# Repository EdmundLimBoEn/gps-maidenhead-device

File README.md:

# Maidenhead Pocket Locator

Open hardware and software for a compact GNSS-powered six-character Maidenhead
locator. The product requirements and validation gates live in [PLAN.md](PLAN.md).

## Current status

The development source tree covers RP2040 firmware and host tests, a
Tk/serial configurator with profiles and UF2 recovery, KiCad engineering sources
and manufacturing workflow, a parametric enclosure with printable exports, and
assembly/validation documentation.

This is **not yet a physically validated product release**. Ordering and public
distribution remain gated on the frozen BOM/quote, reviewed manufacturing exports,
prototype bring-up, and measured acceptance evidence listed in
[the release checklist](docs/manufacturing/RELEASE_CHECKLIST.md) and
[evidence index](docs/testing/TEST_EVIDENCE.md). No claim is made here that the
weather, battery, GNSS, off-current, thermal, or cost gates have passed.

## Development

```sh
cmake -S firmware -B .build/firmware
cmake --build .build/firmware
ctest --test-dir .build/firmware --output-on-failure

python -m venv .venv
. .venv/bin/activate
python -m pip install -e './configurator[dev]'
pytest configurator/tests
python -m ruff check configurator tools
python -m ruff format --check configurator tools
python -m maidenhead_configurator

bash firmware/tests/pico_stub_compile.sh
python3 hardware/manufacturing/preflight.py
python3 tools/export_enclosure.py
python3 tools/validate_enclosure.py --require-openscad
python3 tools/check_docs.py
python3 tools/release_preflight.py
```

To build an RP2040 UF2, install the Pico SDK and set its location:

```sh
PICO_SDK_PATH=/path/to/pico-sdk \
  cmake -S firmware -B .build/firmware-pico -DPOCKET_LOCATOR_BUILD_RP2040=ON
cmake --build .build/firmware-pico
```

The GUI starts against a simulator by default. A physical device uses
newline-delimited JSON over USB CDC; each configuration write includes a fresh
15-year named-zone transition table. Profiles remain location-free and portable.

## Manufacturing and safety

Do not order or distribute from an arbitrary working tree. Generate artifacts from
a tagged revision, complete [the five-unit order package](docs/manufacturing/ORDER_PACKAGE.md),
and follow the [assembly](docs/assembly/ASSEMBLY.md) and
[test procedures](docs/testing/TEST_PROCEDURES.md).

The [mechanical interface contract](enclosure/INTERFACES.md) and
[cost research snapshot](docs/manufacturing/COST_RESEARCH.md) make the remaining
fit and landed-cost unknowns explicit. Neither is a manufacturing sign-off.

Use only the released protected LiPo and charger configuration. The device is not
an emergency locator, navigation instrument, tracker, or immersion-rated product.
Do not charge it while wet or leave it charging in a hot vehicle.

## Licensing

Firmware and configurator code are GPL-3.0-or-later. Hardware and mechanical
sources are CERN-OHL-S-2.0. Documentation is CC-BY-SA-4.0. See [LICENSES](LICENSES/README.md).

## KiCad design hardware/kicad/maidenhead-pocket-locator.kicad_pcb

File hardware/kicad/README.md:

# Hardware design source

SPDX-License-Identifier: CERN-OHL-S-2.0

This directory contains the revision-A *engineering* KiCad source for the
Maidenhead Pocket Locator.  It is deliberately a source-controlled design,
not by itself a claim that an assembled product has been validated: the selected
LCD, patch antenna, cell and enclosure still require physical fit checks. No RF,
power, charger or thermal measurement has been performed on assembled hardware.

`design.yaml` is a review summary of the electrical architecture and constraints;
the component/pin contract is embedded in `generate_kicad.py`. The generator
writes the legacy schematic and cache while preserving the authoritative routed
PCB. Passing `--force-placement` explicitly replaces the PCB with its
deterministic unrouted placement. The source set contains:

* `maidenhead-pocket-locator.sch` — deterministic legacy Eeschema source;
* `maidenhead-pocket-locator.kicad_sch` — the committed modern KiCad source,
  synchronized from the legacy source with KiCad and used for PDF/netlist exports;
* `maidenhead-pocket-locator.kicad_pcb` — the authoritative routed 4-layer,
  81 x 37 mm board with edge connectors, test points and controlled RF/USB
  net classes. The default manufacturing preflight requires zero DRC errors,
  zero unconnected items, filled inner planes, no signal tracks on In1, and
  only the length-bounded `LCD_RS_3V3`, `LOCATE_N`, `QSPI_SCLK`, and
  `QSPI_SD2` crossovers on In2.

The generated board is useful for electrical/mechanical review and routing
iteration. It must not be sent to a fabricator until the
release checklist passes.  `../manufacturing/export.sh` runs the KiCad CLI
exports and DRC when KiCad is installed.

## Regenerate and inspect

```sh
python3 hardware/kicad/generate_kicad.py
# After an intentional electrical edit, open the legacy .sch in the pinned KiCad
# version, save the converted modern .kicad_sch, and run preflight to compare them.
# Only when intentionally restarting layout:
python3 hardware/kicad/generate_kicad.py --force-placement
python3 hardware/manufacturing/preflight.py --source-only
python3 hardware/manufacturing/preflight.py
kicad hardware/kicad/maidenhead-pocket-locator.kicad_pro
```

The source-only command is a diagnostic aid. CI and manufacturing exports use
the strict default command; it must pass before manufacturing exports are
accepted.

The board datum is the lower-left outside corner.  LCD/window centre is
`(40.5, 18.5)`.  The antenna is an enclosure-mounted patch, not a PCB
component; its 50-ohm route ends at J4.  Keep the top-wall patch projection
clear of copper and parts as documented in `../RF_AND_LAYOUT.md`.

The controlled stack is F.Cu signal/power, In1 uninterrupted GND reference,
In2 predominantly 3V3 power distribution, and B.Cu signal/GND. In2 carries only
the under-7 mm LCD RS, under-4 mm LOCATE, and under-6 mm QSPI SCLK/SD2
crossovers allowlisted by preflight. USB and GNSS RF stay on outer copper over
In1; the short QSPI inner runs also reference the uninterrupted In1 plane. Obtain
the fabricator's impedance calculation before release; nominal
trace widths in the source are starting values, not a substitute for a coupon.
Ordinary logic uses 0.15 mm traces and 0.50/0.20 mm through-vias. Dense QSPI
fanout uses 0.10 mm traces and local 0.46/0.20 mm standard through-vias; confirm
the 0.13 mm annular ring with the selected fabricator. The edge rule
is 0.20 mm for the unavoidable short escapes at J1, SW1 and SW2; confirm both
capabilities in the selected board quote.

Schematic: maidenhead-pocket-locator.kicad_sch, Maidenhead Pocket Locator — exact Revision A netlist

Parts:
C1, C2, C3, C4, C5, C6, C7, C8, C9: 100nF; C_0402_1005Metric
CADC1: 1uF; C_0603_1608Metric
CBAT1: 4.7uF; C_0603_1608Metric
CBATADC1: 100nF; C_0402_1005Metric
CBBIN1: 10uF; C_0805_2012Metric
CBBOUT1: 22uF; C_0805_2012Metric
CDV1, CDV2: 100nF; C_0402_1005Metric
CFLASH1: 100nF; C_0402_1005Metric
CGIN1: 1uF; C_0402_1005Metric
CGNSS1: 100nF; C_0402_1005Metric
CGNSS2: 820pF; C_0402_1005Metric
CGNSS3: 10uF; C_0805_2012Metric
CGOUT1: 4.7uF; C_0603_1608Metric
CIN1: 1uF; C_0603_1608Metric
CLCDIN1: 10uF; C_0805_2012Metric
CLCDO1, CLCDO2: 10uF; C_0805_2012Metric
COUT1: 4.7uF; C_0603_1608Metric
CRESET1: 100nF; C_0402_1005Metric
CULD1: 100nF; C_0402_1005Metric
CULS1: 100nF; C_0402_1005Metric
CVREG1: 1uF; C_0603_1608Metric
CX1, CX2: 15pF; C_0402_1005Metric
D1: TPD2EUSB30DRTR; Texas_DRT0003A
D2, D4: BAT54H; D_SOD-323
D3, D5: 1N4148WS; D_SOD-323
F1: MF-MSMF050-2; Fuse_1812_4532Metric
J1: USB4105-GF-A
J2: B3B-PH-K-S(LF)(SN); JST_PH_B3B-PH-K_1x03_P2.00mm_Vertical
J3: 61301611121; PinHeader_1x16_P2.54mm_Vertical
J4: Hirose 20449-001E; U.FL_Hirose_U.FL-R-SMT-1_Vertical
LBB1: XFL4020-471MEC; L_Coilcraft_XxL4020
LED1: KP-2012EC; LED_0805_2012Metric
LLCD1: LQH2MCN1R0M02L; L_0805_2012Metric
Q1, Q4: DMP3098L-7; SOT-23
Q2, Q3, Q5: DMN2050L-7; SOT-23
RBAT1, RBAT2: 100k; R_0402_1005Metric
RBATG1: 100k; R_0402_1005Metric
RBB1: 511k; R_0402_1005Metric
RBB2: 91k; R_0402_1005Metric
RBL1: 68R; R_0603_1608Metric
RBOOT1: 1k; R_0402_1005Metric
RCC1, RCC2: 5.1k; R_0402_1005Metric
RCHG1: 1k; R_0402_1005Metric
RCHGPU1: 100k; R_0402_1005Metric
REN1: 1M; R_0402_1005Metric
RGNSSEN1: 100k; R_0402_1005Metric
RGNSSRX1: 33R; R_0402_1005Metric
RGNSSTX1: 33R; R_0402_1005Metric
RHOLD1: 100k; R_0402_1005Metric
RILIM1: 2.00k; R_0402_1005Metric
RISET1: 2.20k; R_0402_1005Metric
RITERM1: 3.30k; R_0402_1005Metric
RLCD1: 909k; R_0402_1005Metric
RLCD2: 100k; R_0402_1005Metric
RLCDEN1: 100k; R_0402_1005Metric
RLOC1: 100k; R_0402_1005Metric
ROFF1: 100k; R_0402_1005Metric
RRESET1: 100k; R_0402_1005Metric
RSENSEEN1: 100k; R_0402_1005Metric
RSTART1: 100k; R_0402_1005Metric
RTMR1: 48.7k; R_0402_1005Metric
RUSB1, RUSB2: 27R; R_0402_1005Metric
RVB1: 82k; R_0402_1005Metric
RVB2: 100k; R_0402_1005Metric
RVO1: 4.7k; R_0402_1005Metric
RVO2: 560R; R_0402_1005Metric
RXTAL1: 1k; R_0402_1005Metric
SW1, SW2: TL1014BF160QG; SW_TL1014B
SW3, SW4: EVQ-P7A01P; SW_SPST_EVQP7A
TH1: 10k NTC DNP; R_0603_1608Metric
TP1: VBUS; TestPoint_Pad_D1.5mm
TP2: BAT; TestPoint_Pad_D1.5mm
TP3: SYS_RAW; TestPoint_Pad_D1.5mm
TP4: 3V3; TestPoint_Pad_D1.5mm
TP5: 5V_LCD; TestPoint_Pad_D1.5mm
TP6: GND; TestPoint_Pad_D1.5mm
TP7: POWER_HOLD; TestPoint_Pad_D1.5mm
TP8: GNSS_TX; TestPoint_Pad_D1.5mm
TP9: GNSS_RX; TestPoint_Pad_D1.5mm
TP10: SWDIO; TestPoint_Pad_D1.5mm
TP11: SWCLK; TestPoint_Pad_D1.5mm
TP12: RUN_N; TestPoint_Pad_D1.5mm
TP13: BOOTSEL_N; TestPoint_Pad_D1.5mm
U1: RP2040; QFN-56-1EP_7x7mm_P0.4mm_EP3.2x3.2mm
U2: W25Q16JVUXIQ; Winbond_UX_8
U3: BQ24074RGTR; Texas_RGT0016C
U4: TPS63802DLAR; Texas_DLA0010A
U5: TPS61023DRLR; SOT-563
U6: SN74LVC8T245PWR; TSSOP-24_4.4x7.8mm_P0.65mm
U7: Ai-Thinker GP-02; GP-02
U8: TPS22916BYFPR; Texas_YFP0004
X1: ABM8-272-T3; Crystal_SMD_Abracon_ABM8G-4Pin_3.2x2.5mm

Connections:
1V1: CDV1.1 (1V1), CDV2.1 (1V1), CVREG1.1 (1V1), U1.23 (1V1), U1.45 (1V1), U1.50 (1V1)
3V3: C1.1 (3V3), C2.1 (3V3), C3.1 (3V3), C4.1 (3V3), C5.1 (3V3), C6.1 (3V3), C7.1 (3V3), C8.1 (3V3), C9.1 (3V3), CADC1.1 (3V3), CBBOUT1.1 (3V3), CFLASH1.1 (3V3), CGIN1.1 (3V3), CULS1.1 (3V3), RBB1.1 (3V3), RCHG1.1 (3V3), RCHGPU1.1 (3V3), RLOC1.1 (3V3), ROFF1.1 (3V3), RRESET1.1 (3V3), TP4.1, U1.1 (3V3), U1.10 (3V3), U1.22 (3V3), U1.33 (3V3), U1.42 (3V3), U1.43 (3V3), U1.44 (3V3), U1.48 (3V3), U1.49 (3V3), U2.8 (3V3), U4.6 (3V3), U6.1 (3V3), U6.2 (3V3), U8.A2 (3V3)
3V3_GNSS: CGNSS1.1 (3V3_GNSS), CGNSS2.1 (3V3_GNSS), CGNSS3.1 (3V3_GNSS), CGOUT1.1 (3V3_GNSS), U7.8 (3V3_GNSS), U8.A1 (3V3_GNSS)
5V_LCD: CLCDO1.1 (5V_LCD), CLCDO2.1 (5V_LCD), CULD1.1 (5V_LCD), J3.2 (5V_LCD), RBL1.1 (5V_LCD), RLCD1.1 (5V_LCD), RVO1.1 (5V_LCD), TP5.1, U5.6 (5V_LCD), U6.23 (5V_LCD), U6.24 (5V_LCD)
BAT: CBAT1.1 (BAT), J2.1 (BAT), Q4.2 (BAT), RBATG1.1 (BAT), TP2.1, U3.2 (BAT), U3.3 (BAT)
BAT_ADC: CBATADC1.1 (BAT_ADC), RBAT1.2 (BAT_ADC), RBAT2.1 (BAT_ADC), U1.38 (BAT_ADC)
BAT_SENSE_EN: Q5.1 (BAT_SENSE_EN), RSENSEEN1.1 (BAT_SENSE_EN), U1.32 (BAT_SENSE_EN)
BAT_SENSE_GATE: Q4.1 (BAT_SENSE_GATE), Q5.3 (BAT_SENSE_GATE), RBATG1.2 (BAT_SENSE_GATE)
BAT_SENSE_SW: Q4.3 (BAT_SENSE_SW), RBAT1.1 (BAT_SENSE_SW)
BB_FB: RBB1.2 (BB_FB), RBB2.1 (BB_FB), U4.4 (BB_FB)
BB_SW1: LBB1.1 (BB_SW1), U4.9 (BB_SW1)
BB_SW2: LBB1.2 (BB_SW2), U4.7 (BB_SW2)
BL_PWM: Q3.1 (BL_PWM), U1.15 (BL_PWM)
BOOTSEL_N: RBOOT1.2 (BOOTSEL_N), SW3.1 (BOOTSEL_N), TP13.1
CC1: J1.A5 (CC1), RCC1.1 (CC1)
CC2: J1.B5 (CC2), RCC2.1 (CC2)
CHG_ILIM: RILIM1.1 (CHG_ILIM), U3.12 (CHG_ILIM)
CHG_ISET: RISET1.1 (CHG_ISET), U3.16 (CHG_ISET)
CHG_ITERM: RITERM1.1 (CHG_ITERM), U3.15 (CHG_ITERM)
CHG_LED_A: LED1.2 (CHG_LED_A), RCHG1.2 (CHG_LED_A)
CHG_N: LED1.1 (CHG_N), RCHGPU1.2 (CHG_N), U1.31 (CHG_N), U3.9 (CHG_N)
CHG_TMR: RTMR1.1 (CHG_TMR), U3.14 (CHG_TMR)
CHG_TS: J2.2 (CHG_TS), TH1.1 (CHG_TS), U3.1 (CHG_TS)
GND: C1.2 (GND), C2.2 (GND), C3.2 (GND), C4.2 (GND), C5.2 (GND), C6.2 (GND), C7.2 (GND), C8.2 (GND), C9.2 (GND), CADC1.2 (GND), CBAT1.2 (GND), CBATADC1.2 (GND), CBBIN1.2 (GND), CBBOUT1.2 (GND), CDV1.2 (GND), CDV2.2 (GND), CFLASH1.2 (GND), CGIN1.2 (GND), CGNSS1.2 (GND), CGNSS2.2 (GND), CGNSS3.2 (GND), CGOUT1.2 (GND), CIN1.2 (GND), CLCDIN1.2 (GND), CLCDO1.2 (GND), CLCDO2.2 (GND), COUT1.2 (GND), CRESET1.2 (GND), CULD1.2 (GND), CULS1.2 (GND), CVREG1.2 (GND), CX1.2 (GND), CX2.2 (GND), D1.3 (GND), J1.A1 (GND), J1.A12 (GND), J1.B1 (GND), J1.B12 (GND), J1.S1 (GND), J2.3 (GND), J3.1 (GND), J3.5 (GND), J3.7 (GND), J3.8 (GND), J3.9 (GND), J3.10 (GND), J4.2 (GND), Q2.2 (GND), Q3.2 (GND), Q5.2 (GND), RBAT2.2 (GND), RBB2.2 (GND), RCC1.2 (GND), RCC2.2 (GND), REN1.2 (GND), RGNSSEN1.2 (GND), RHOLD1.2 (GND), RILIM1.2 (GND), RISET1.2 (GND), RITERM1.2 (GND), RLCD2.2 (GND), RLCDEN1.2 (GND), RSENSEEN1.2 (GND), RTMR1.2 (GND), RVB2.2 (GND), RVO2.2 (GND), SW1.2 (GND), SW1.4 (GND), SW2.2 (GND), SW2.4 (GND), SW3.2 (GND), SW4.2 (GND), TH1.2 (GND), TP6.1, U1.19 (GND), U1.57 (GND), U2.4 (GND), U3.4 (GND), U3.5 (GND), U3.8 (GND), U3.17 (GND), U4.2 (GND), U4.3 (GND), U4.8 (GND), U5.4 (GND), U6.9 (GND), U6.10 (GND), U6.11 (GND), U6.12 (GND), U6.13 (GND), U6.22 (GND), U7.1 (GND), U7.10 (GND), U7.12 (GND), U8.B1 (GND), X1.2 (GND), X1.4 (GND)
GNSS_EN: RGNSSEN1.1 (GNSS_EN), U1.29 (GNSS_EN), U8.B2 (GNSS_EN)
GNSS_PPS: U7.4 (GNSS_PPS)
GNSS_RF_50R: J4.1 (GNSS_RF_50R), U7.11 (GNSS_RF_50R)
GNSS_RX: RGNSSRX1.1 (GNSS_RX), TP9.1, U1.27 (GNSS_RX)
GNSS_RX_U7: RGNSSRX1.2 (GNSS_RX_U7), U7.3 (GNSS_RX_U7)
GNSS_TX: RGNSSTX1.2 (GNSS_TX), TP8.1, U1.28 (GNSS_TX)
GNSS_TX_U7: RGNSSTX1.1 (GNSS_TX_U7), U7.2 (GNSS_TX_U7)
LCD_BL_A: J3.15 (LCD_BL_A), RBL1.2 (LCD_BL_A)
LCD_BL_K: J3.16 (LCD_BL_K), Q3.3 (LCD_BL_K)
LCD_D4: J3.11 (LCD_D4), U6.19 (LCD_D4)
LCD_D4_3V3: U1.11 (LCD_D4_3V3), U6.5 (LCD_D4_3V3)
LCD_D5: J3.12 (LCD_D5), U6.18 (LCD_D5)
LCD_D5_3V3: U1.12 (LCD_D5_3V3), U6.6 (LCD_D5_3V3)
LCD_D6: J3.13 (LCD_D6), U6.17 (LCD_D6)
LCD_D6_3V3: U1.13 (LCD_D6_3V3), U6.7 (LCD_D6_3V3)
LCD_D7: J3.14 (LCD_D7), U6.16 (LCD_D7)
LCD_D7_3V3: U1.14 (LCD_D7_3V3), U6.8 (LCD_D7_3V3)
LCD_E: J3.6 (LCD_E), U6.20 (LCD_E)
LCD_E_3V3: U1.9 (LCD_E_3V3), U6.4 (LCD_E_3V3)
LCD_FB: RLCD1.2 (LCD_FB), RLCD2.1 (LCD_FB), U5.1 (LCD_FB)
LCD_POWER_EN: RLCDEN1.1 (LCD_POWER_EN), U1.7 (LCD_POWER_EN), U5.2 (LCD_POWER_EN)
LCD_RS: J3.4 (LCD_RS), U6.21 (LCD_RS)
LCD_RS_3V3: U1.8 (LCD_RS_3V3), U6.3 (LCD_RS_3V3)
LCD_SW: LLCD1.2 (LCD_SW), U5.5 (LCD_SW)
LCD_VO: J3.3 (LCD_VO), RVO1.2 (LCD_VO), RVO2.1 (LCD_VO)
LOCATE_N: D5.2 (LOCATE_N), RLOC1.2 (LOCATE_N), U1.4 (LOCATE_N)
LOCATE_RAW: D3.1 (LOCATE_RAW), D5.1 (LOCATE_RAW), SW1.1 (LOCATE_RAW), SW1.3 (LOCATE_RAW)
OFF_N: ROFF1.2 (OFF_N), SW2.1 (OFF_N), SW2.3 (OFF_N), U1.5 (OFF_N)
POWER_HOLD: Q2.1 (POWER_HOLD), RHOLD1.1 (POWER_HOLD), TP7.1, U1.6 (POWER_HOLD)
PWR_EN: D2.1 (PWR_EN), D4.1 (PWR_EN), REN1.1 (PWR_EN), U4.1 (PWR_EN)
PWR_START_GATE: D3.2 (PWR_START_GATE), Q1.1 (PWR_START_GATE), Q2.3 (PWR_START_GATE), RSTART1.2 (PWR_START_GATE)
PWR_START_OUT: D4.2 (PWR_START_OUT), Q1.3 (PWR_START_OUT)
QSPI_CSN: RBOOT1.1 (QSPI_CSN), U1.56 (QSPI_CSN), U2.1 (QSPI_CSN)
QSPI_SCLK: U1.52 (QSPI_SCLK), U2.6 (QSPI_SCLK)
QSPI_SD0: U1.53 (QSPI_SD0), U2.5 (QSPI_SD0)
QSPI_SD1: U1.55 (QSPI_SD1), U2.2 (QSPI_SD1)
QSPI_SD2: U1.54 (QSPI_SD2), U2.3 (QSPI_SD2)
QSPI_SD3: U1.51 (QSPI_SD3), U2.7 (QSPI_SD3)
RUN_N: CRESET1.1 (RUN_N), RRESET1.2 (RUN_N), SW4.1 (RUN_N), TP12.1, U1.26 (RUN_N)
SWCLK: TP11.1, U1.24 (SWCLK)
SWDIO: TP10.1, U1.25 (SWDIO)
SYS_RAW: CBBIN1.1 (SYS_RAW), CLCDIN1.1 (SYS_RAW), COUT1.1 (SYS_RAW), LLCD1.1 (SYS_RAW), Q1.2 (SYS_RAW), RSTART1.1 (SYS_RAW), TP3.1, U3.10 (SYS_RAW), U3.11 (SYS_RAW), U4.10 (SYS_RAW), U5.3 (SYS_RAW)
USB_DM: RUSB2.2 (USB_DM), U1.46 (USB_DM)
USB_DM_CONN: D1.2 (USB_DM_CONN), J1.A7 (USB_DM_CONN), J1.B7 (USB_DM_CONN), RUSB2.1 (USB_DM_CONN)
USB_DP: RUSB1.2 (USB_DP), U1.47 (USB_DP)
USB_DP_CONN: D1.1 (USB_DP_CONN), J1.A6 (USB_DP_CONN), J1.B6 (USB_DP_CONN), RUSB1.1 (USB_DP_CONN)
VBUS: CIN1.1 (VBUS), D2.2 (VBUS), F1.2 (VBUS), RVB1.1 (VBUS), TP1.1, U3.6 (VBUS), U3.13 (VBUS)
VBUS_PRESENT: RVB1.2 (VBUS_PRESENT), RVB2.1 (VBUS_PRESENT), U1.30 (VBUS_PRESENT)
VBUS_RAW: F1.1 (VBUS_RAW), J1.A4 (VBUS_RAW), J1.A9 (VBUS_RAW), J1.B4 (VBUS_RAW), J1.B9 (VBUS_RAW)
XIN: CX1.1 (XIN), U1.20 (XIN), X1.1 (XIN)
XOUT: RXTAL1.1 (XOUT), U1.21 (XOUT)
XOUT_XTAL: CX2.1 (XOUT_XTAL), RXTAL1.2 (XOUT_XTAL), X1.3 (XOUT_XTAL)

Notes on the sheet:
BQ24074 OUT is the sole SYS_RAW source. J1 VBUS_RAW passes through F1 to VBUS.
EXACT PAD-NUMBER NETLIST — all unassigned physical pads are explicit no-connects

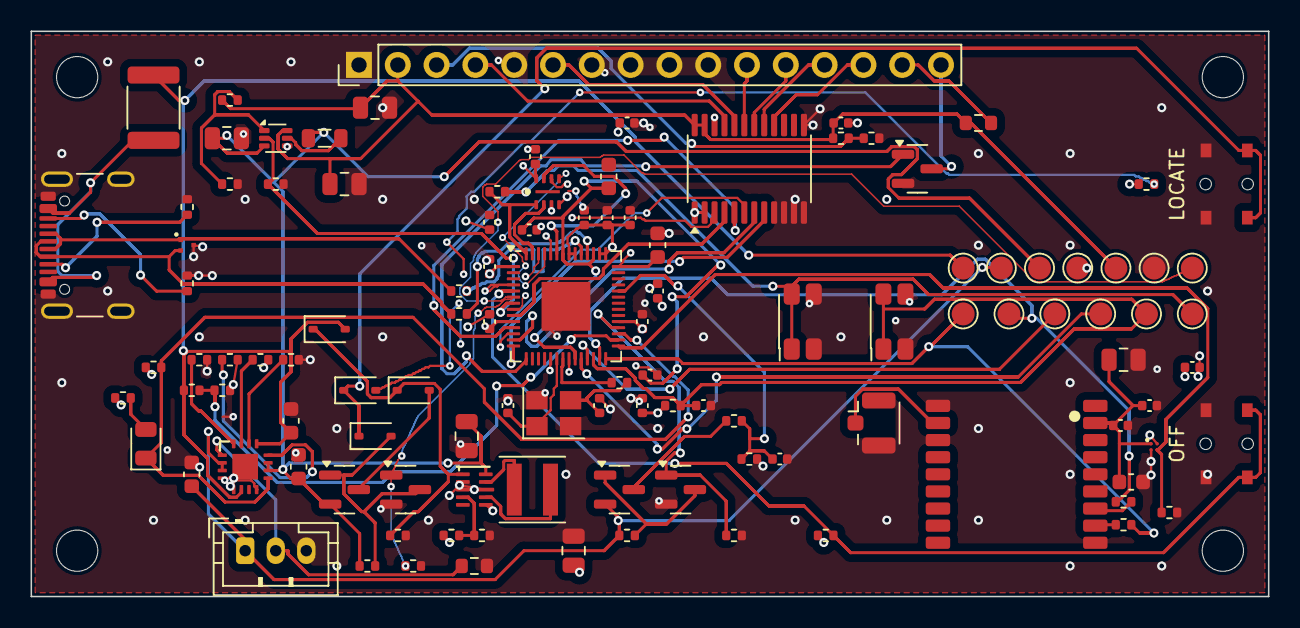
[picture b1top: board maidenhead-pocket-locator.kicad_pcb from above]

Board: 4 copper layers, 81.0 x 37.0 mm, 117 parts (0 on the bottom side), 75 nets.

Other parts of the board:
H1, H2, H3, H4: M2.5; MountingHole_2.7mm_M2.5

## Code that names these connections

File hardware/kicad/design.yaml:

# SPDX-License-Identifier: CERN-OHL-S-2.0
# Connected Revision-A electrical contract. Purchased-part drawings and bench
# results remain mandatory release gates.
project: maidenhead-pocket-locator
revision: A-electrical
board:
  width_mm: 81.0
  height_mm: 37.0
  layers: 4
  thickness_mm: 1.6
  stackup: "F.Cu signal/power, In1 solid GND, In2 3V3 power with LCD_RS_3V3 under 7 mm, LOCATE_N under 4 mm, and QSPI_SCLK/QSPI_SD2 under 6 mm, B.Cu signal/GND; USB and RF stay outer-layer; freeze vendor dielectric and recalculate USB/RF impedance before release"
power_architecture:
  charger_source: "BQ24074 OUT is the sole SYS_RAW source; BAT never bypasses OUT"
  system_regulator: "TPS63802DLAR adjustable buck-boost, 3.3 V, 0.47 uH, 511k/91k feedback"
  start_logic: "TPS63802 EN is diode-OR of USB VBUS and Q1 signal-PMOS output"
  locate_start: "SW1 pulls isolated LOCATE_RAW low; D3 starts Q1 and D5 reports LOCATE_N without an off-state 3V3-to-latch path"
  usb_idle: "VBUS forces 3V3 only; GPIO5 LCD_POWER_EN and GPIO18 GNSS_EN default low"
  off_state: "TPS63802 shutdown; charger/protected cell and signal latch remain BAT-connected"
nets:
  power: [VBUS, BAT, SYS_RAW, PWR_EN, 3V3, 1V1, 3V3_GNSS, 5V_LCD, GND]
  usb: [VBUS_RAW, USB_DP_CONN, USB_DM_CONN, USB_DP, USB_DM, CC1, CC2]
  control: [LOCATE_N, OFF_N, POWER_HOLD, LCD_POWER_EN, GNSS_EN, BAT_SENSE_EN, VBUS_PRESENT, CHG_N]
  gnss: [GNSS_TX, GNSS_RX, GNSS_PPS, GNSS_RF_50R]
  lcd: [LCD_RS, LCD_E, LCD_D4, LCD_D5, LCD_D6, LCD_D7, LCD_BL_A, LCD_BL_K, BL_PWM]
components:
  - {ref: U1, mpn: RP2040, package: "QFN-56 7x7", role: MCU}
  - {ref: U2, mpn: W25Q16JVUXIQ, package: "USON-8 2x3", role: boot_flash}
  - {ref: U3, mpn: BQ24074RGTR, package: "VQFN-16 3x3", role: power_path_charger}
  - {ref: U4, mpn: TPS63802DLAR, package: "VSON-HR-10 3x2", role: 3v3_buck_boost}
  - {ref: U5, mpn: TPS61023DRLR, package: "SOT-563-6", role: lcd_boost}
  - {ref: U6, mpn: SN74LVC8T245PWR, package: TSSOP-24, role: lcd_level_shift}
  - {ref: U7, mpn: Ai-Thinker-GP-02, package: "SMD-18 9.9x10.3 mm P1.12 manufacturer land", role: GNSS}
  - {ref: U8, mpn: TPS22916BYFPR, package: "YFP DSBGA-4 0.78x0.78 mm P0.4", role: gnss_load_switch}
  - {ref: Q1, mpn: DMP3098L-7, role: signal_only_start_switch}
  - {ref: Q2, mpn: DMN2050L-7, role: power_hold_gate_pull_down}
  - {ref: Q3, mpn: DMN2050L-7, role: lcd_backlight_pwm}
  - {ref: Q4, mpn: DMP3098L-7, role: battery_divider_high_side}
  - {ref: Q5, mpn: DMN2050L-7, role: battery_divider_gate}
  - {ref: J1, mpn: GCT_USB4105-GF-A, role: USB-C_device}
  - {ref: J2, mpn: "B3B-PH-K-S(LF)(SN)", role: protected_cell_NTC}
  - {ref: J3, mpn: "61301611121", role: lcd_header}
  - {ref: J4, mpn: "20449-001E", role: GNSS_uFL}
firmware_contract:
  GPIO2: LOCATE_N
  GPIO3: OFF_N
  GPIO4: POWER_HOLD
  GPIO5: LCD_POWER_EN
  GPIO6: LCD_RS_3V3
  GPIO7: LCD_E_3V3
  GPIO8: LCD_D4_3V3
  GPIO9: LCD_D5_3V3
  GPIO10: LCD_D6_3V3
  GPIO11: LCD_D7_3V3
  GPIO12: BL_PWM
  GPIO16: GNSS_RX
  GPIO17: GNSS_TX
  GPIO18: GNSS_EN
  GPIO19: VBUS_PRESENT
  GPIO20: CHG_N
  GPIO21: BAT_SENSE_EN
  GPIO26_ADC0: BAT_ADC
release_blockers:
  - "Verify every footprint and pad number against the ordered manufacturer drawing."
  - "Verify the GP-02 and TPS22916 footprints against the ordered lot/package markings before assembly release."
  - "Calculate GNSS 50-ohm CPWG width/clearance from the exact ordered stack-up."
  - "Run KiCad GUI ERC/DRC and archive zero-unreviewed-error reports."
  - "Measure LCD current, charge/NTC, shutdown current, RF and thermal behavior."

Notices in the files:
hardware/kicad/maidenhead-pocket-locator.kicad_sch:
Open hardware — CERN-OHL-S-2.0
